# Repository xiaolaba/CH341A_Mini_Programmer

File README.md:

# CH341A_Mini_Programmer
hardware, software used for  

### update my schematic  
port to KiCAD 8.0.9, no PCB done, only schematic  
[CH341A_modified_MiniProgrammer](CH341A_modified_MiniProgrammer)  KiCAD project files,  

### software used
https://github.com/xiaolaba/UsbAsp-flash_AsProgrammer  
2.03a

IMSProg (fork https://github.com/xiaolaba/IMSProg)  
2026-11-23 try this software, not working ?!  
https://github.com/bigbigmdm/IMSProg/issues/281, Q&A and solution,     
done, short Jumper 1-2, bootstrap and programmer mode, USB VID_1A86 PID_5512  
USB VID_1A86 PID_55523, it UART mode;  

NeoProgrammer  
[https://neoprogrammer.net/](https://neoprogrammer.net/)  

### hardward used
CH341A Mini Programmer 土豪金  
原來5V, 改成 3.3V IO  

REF:  

https://bbs.pigoo.com/thread-84511-1-1.html  
http://diybcq.com/thread-144131-1-1.html  
https://www.onetransistor.eu/2017/08/ch341a-mini-programmer-schematic.html  

### driver
http://www.wch.cn/downloads/CH341PAR_EXE.html  
http://www.wch.cn/downloads/CH341SER_EXE.html

### CH341PAR.EXE, USB programmer  
CH341 	2.2 	2021-10-16 	269KB  
CH341USB转IIC、SPI等接口的WINDOWS驱动，支持32/64位 Windows 11/10/8.1/8/7/VISTA/XP，SERVER 2019/2016/2012/2008/2003， 2000/ME/98，通过微软数字签名认证，支持USB转EPP/MEM并口，支持USB转同步串口：IIC/I2C、SPI等，用于随产品发行到最终用户。  
donwload [CH341SER.ZIP](CH341SER.ZIP) 

### CH341SER.EXE, USB - SERIAL  
CH340G，CH340T，CH340C，CH340N, CH340K, CH340E，CH340B，CH341A，CH341F, CH341T，CH341B，CH341C，CH341U 	3.7 	2022-03-02 	631KB
CH340/CH341 USB转串口WINDOWS驱动程序，支持32/64位Windows 11/10/8.1/8/7/VISTA/XP，SERVER 2022/2019/2016/2012/2008/2003，2000/ME/98，通过微软数字签名认证，支持USB转UART/3线和9线SERIAL串口等，用于随产品发行到最终用户。
 
downaload [CH341PAR.EXE](CH341PAR.EXE)  

### schematic

### modification
cut 5V trace, short pin header 3.3V - 5V, the device will be 3.3V IO and supply to CH341A chip.  

### theory and my workdone, it is great

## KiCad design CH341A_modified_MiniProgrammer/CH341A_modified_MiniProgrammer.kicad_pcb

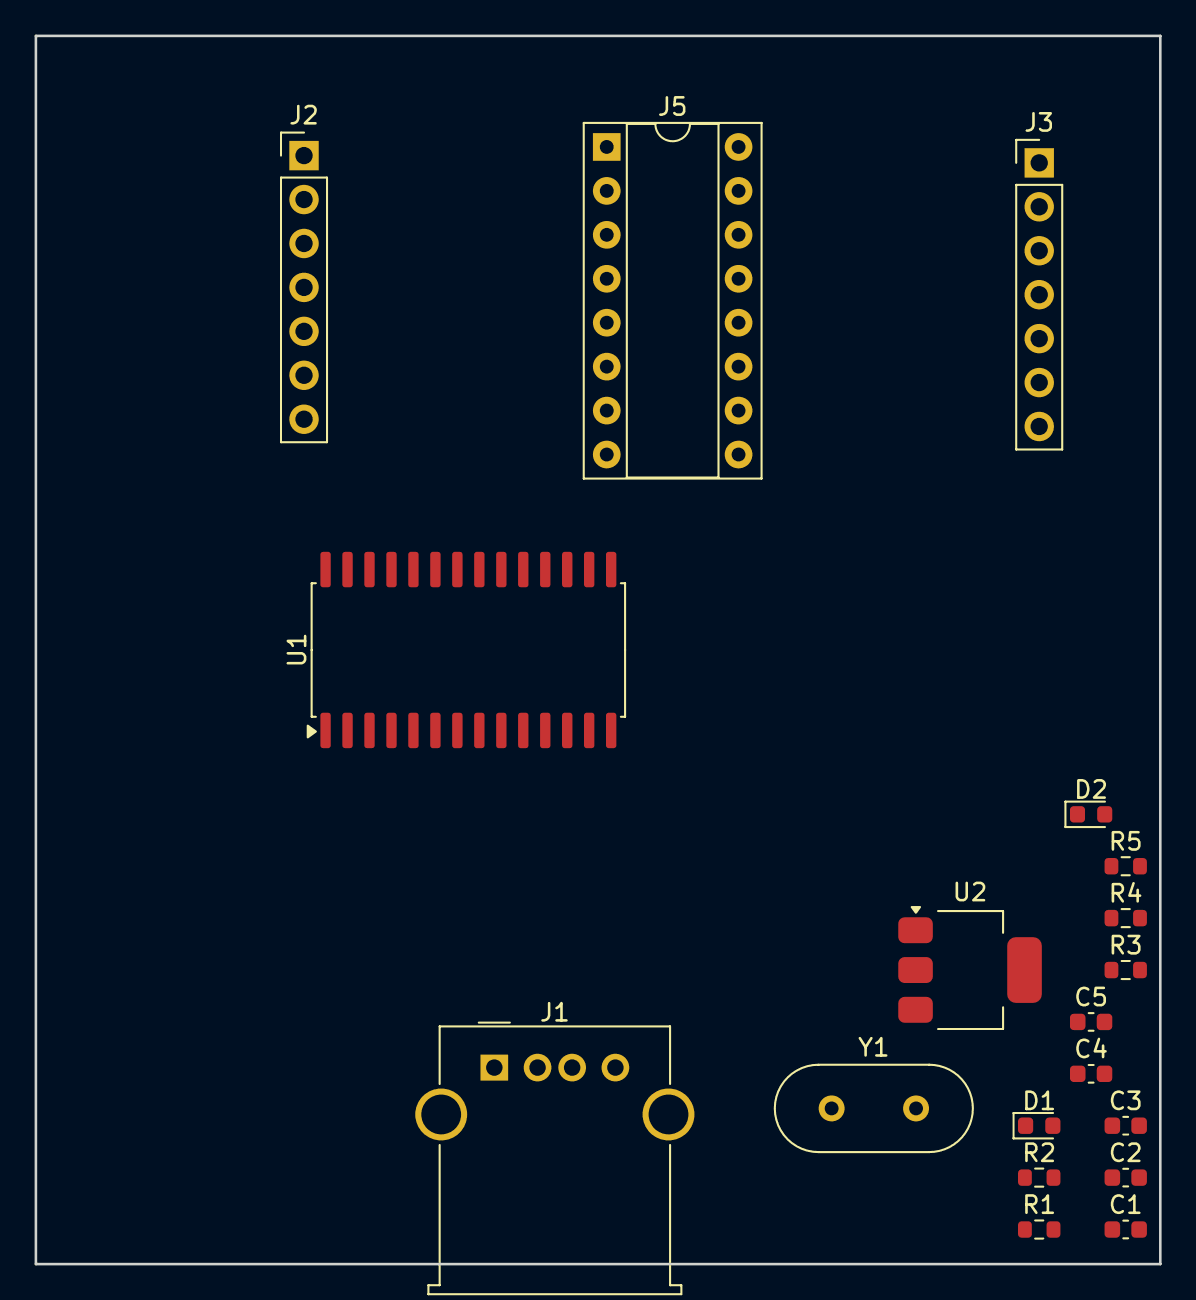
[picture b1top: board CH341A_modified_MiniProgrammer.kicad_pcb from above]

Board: 2 copper layers, 65.0 x 71.0 mm, 19 parts (0 on the bottom side), 21 nets, no tracks yet.

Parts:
C1, C5: 100nF (104); C_0603_1608Metric
C2, C4: 20pF; C_0603_1608Metric
C3: 4.7nF (472); C_0603_1608Metric
D1: POWER; LED_0603_1608Metric
D2: RUN; LED_0603_1608Metric
J1: USB_A; USB_A_Molex_67643_Horizontal
J2: Mode_UART_Header; PinHeader_1x07_P2.54mm_Vertical
J3: SPI_Header; PinHeader_1x07_P2.54mm_Vertical
J5: ZIF_Socket_16; DIP-16_W7.62mm_Socket
R1: 0R; R_0603_1608Metric
R2, R3, R4, R5: 2.2k (222); R_0603_1608Metric
U1: CH341A; SOIC-28W_7.5x17.9mm_P1.27mm
U2: AMS1117-3.3; SOT-223-3_TabPin2
Y1: 12MHz; Crystal_HC49-4H_Vertical

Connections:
+3V3: C5.1, J3.6, J5.7, J5.11, J5.12, J5.16, U2.2 (VO)
+5V: C1.1, R1.2, R2.2, U2.3 (VI)
/ACT_N: J2.1, R3.1
/CLK: J3.1, J5.10, U1.18 (DCD#/D3/DCK)
/CS: J3.2, J5.5, R5.2, U1.15 (CTS#/D0/CS0)
/MISO: J3.4, J5.6, U1.22 (SLP#/D7/DIN)
/MOSI: J3.3, J5.9, U1.20 (DTR#/D5/DOUT)
/RXD: J2.5, U1.6 (RXD/PEMP)
/SCL: J5.14, U1.24 (SCL)
/SDA: J5.13, R4.2, U1.23 (SDA)
/TXD: J2.4, U1.5 (TXD/ERR#)
/USB_DM: J1.2 (D-), U1.11 (UD-)
/USB_DP: J1.3 (D+), U1.10 (UD+)
GND: C1.2, C2.2, C3.1, C4.2, C5.2, D1.2 (A), J1.4 (GND), J2.2, J2.6, J3.5, J5.1, J5.2, J5.3, J5.4, J5.8, J5.15, U1.12 (GND), U2.1 (GND)
unnamed: D1.1 (K), R2.1
unnamed: D2.2 (A), R4.1, R5.1
unnamed: R3.2, U1.1 (ACT#)
unnamed: C3.2, U1.9 (V3)
unnamed: C2.1, U1.13 (XI), Y1.1
unnamed: C4.1, U1.14 (XO), Y1.2
VCC: J2.7, J3.7, U1.28 (VCC)
